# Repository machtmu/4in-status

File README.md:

# Status Module Repository

---

<div align="center">
  <div>

    <p><em>3D Render</em></p>
  </div>
  <br>

  <div>
    <br>
    <p><em>Schematic</em></p>
  </div>
  <br>
  
  <div>
    
    <br>
    <em>Footprint</em>
  </div>
</div>

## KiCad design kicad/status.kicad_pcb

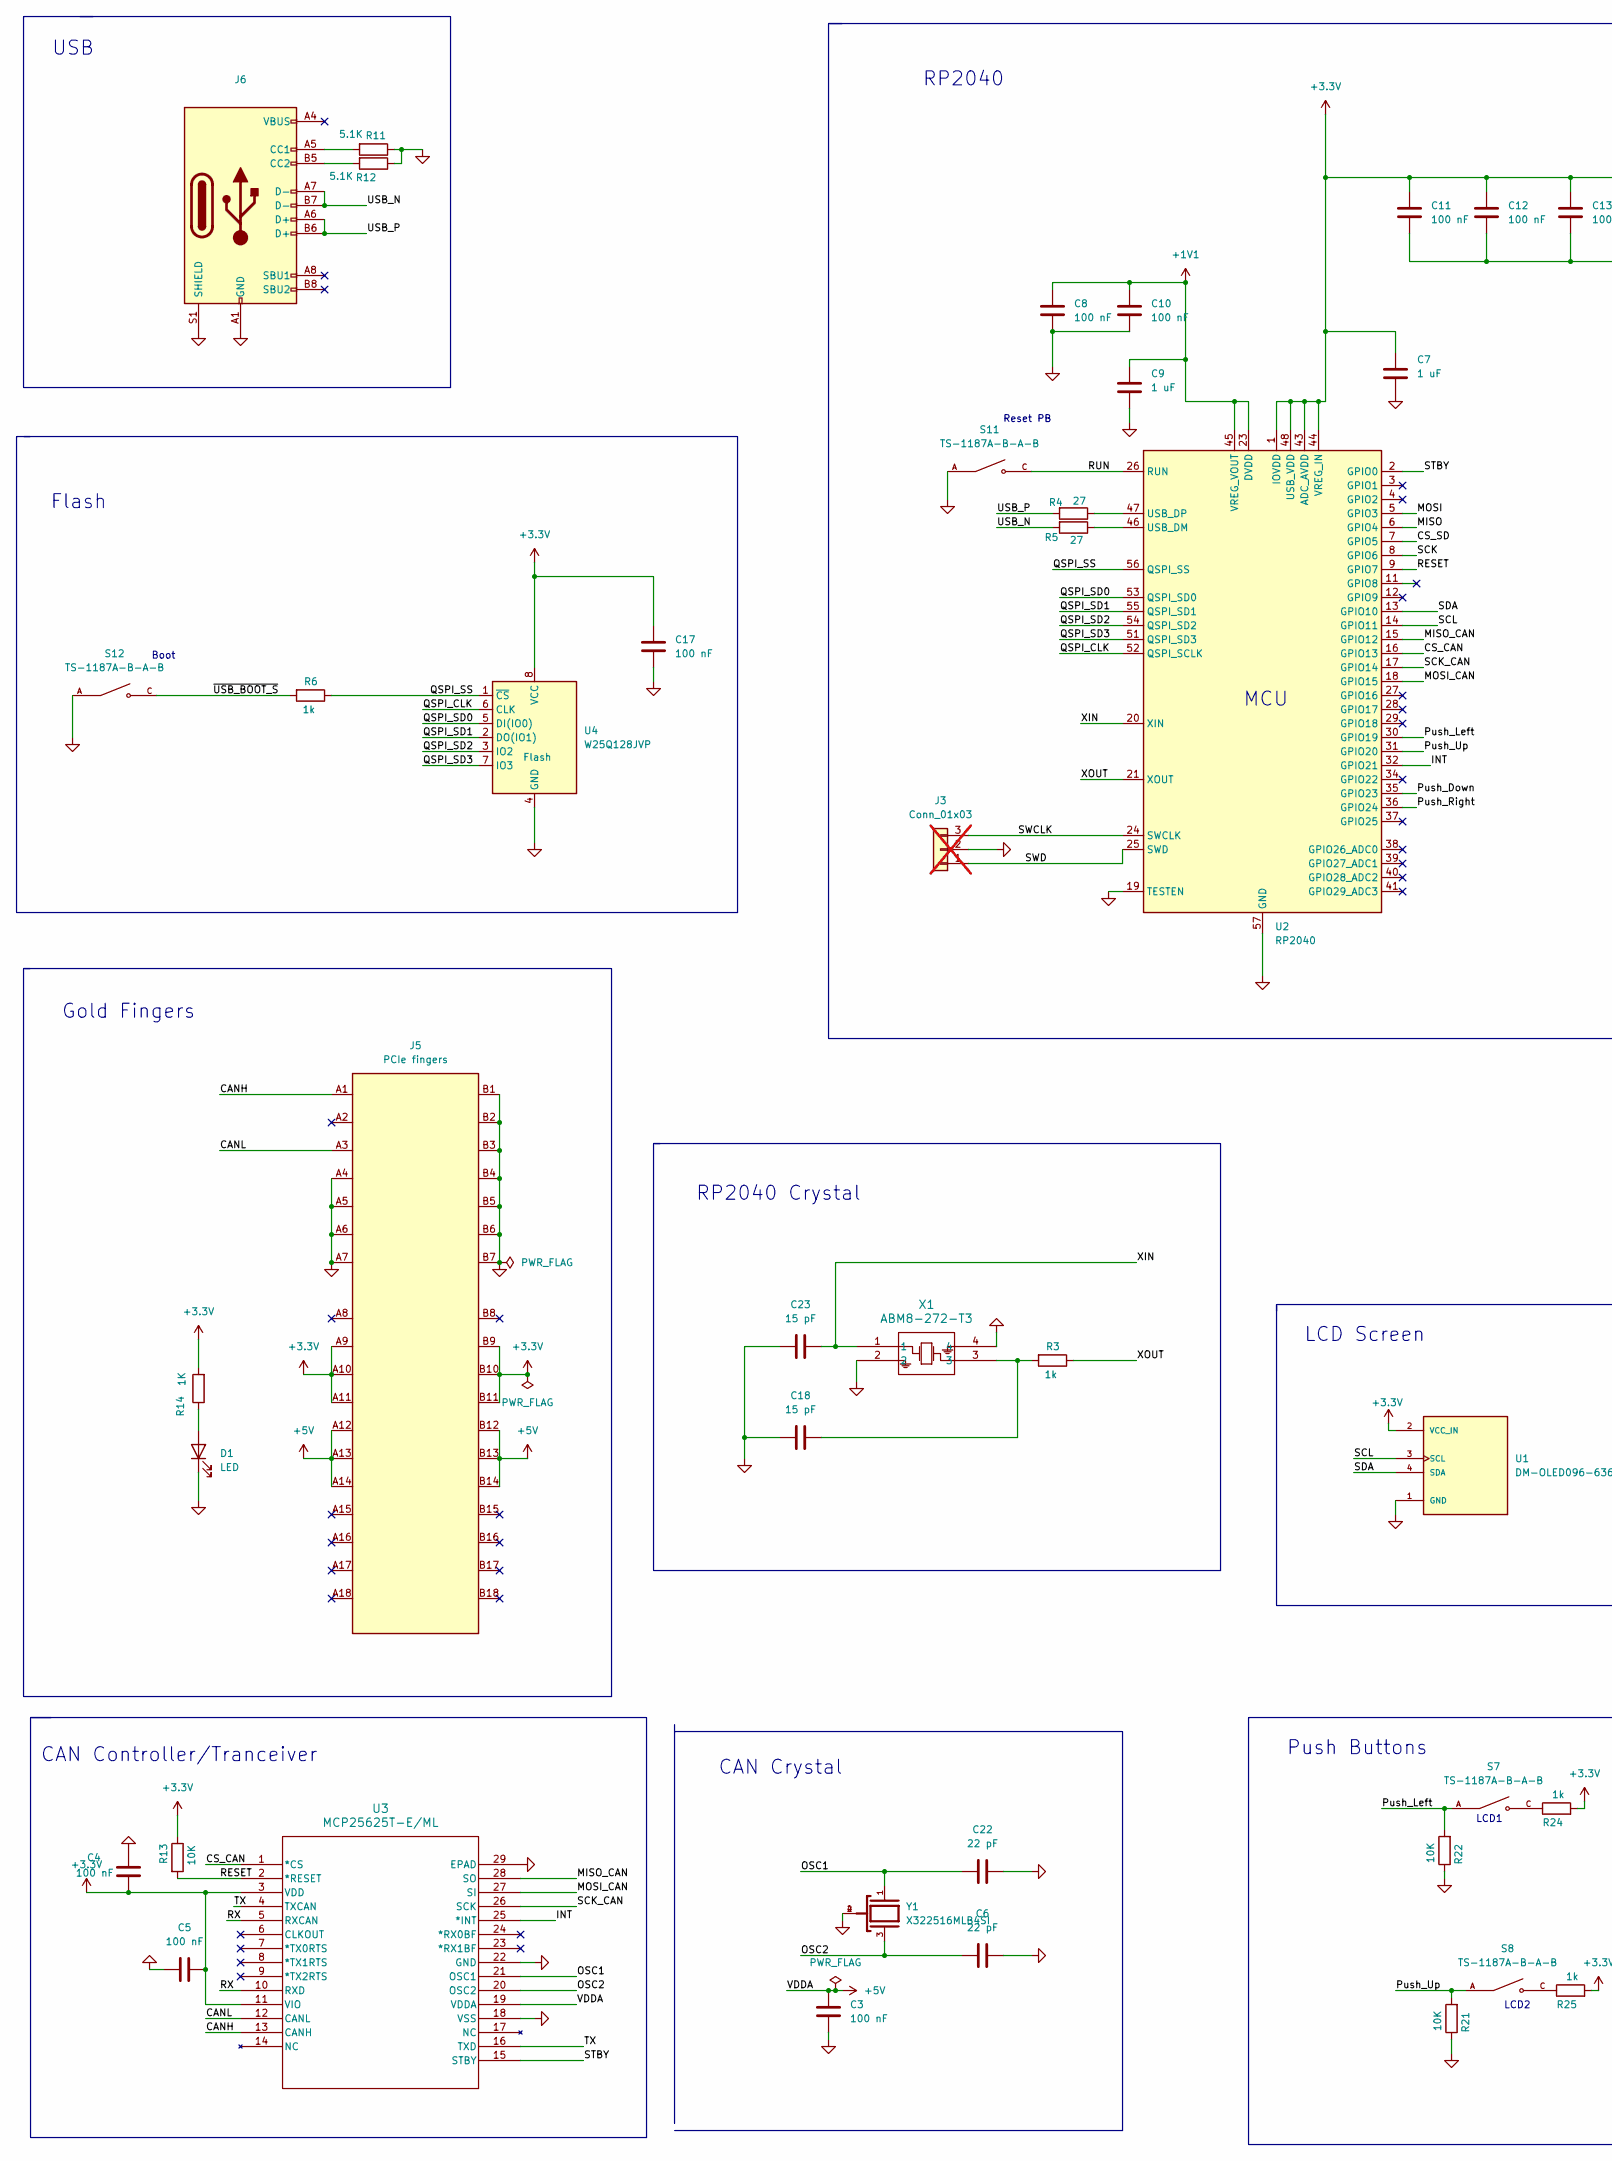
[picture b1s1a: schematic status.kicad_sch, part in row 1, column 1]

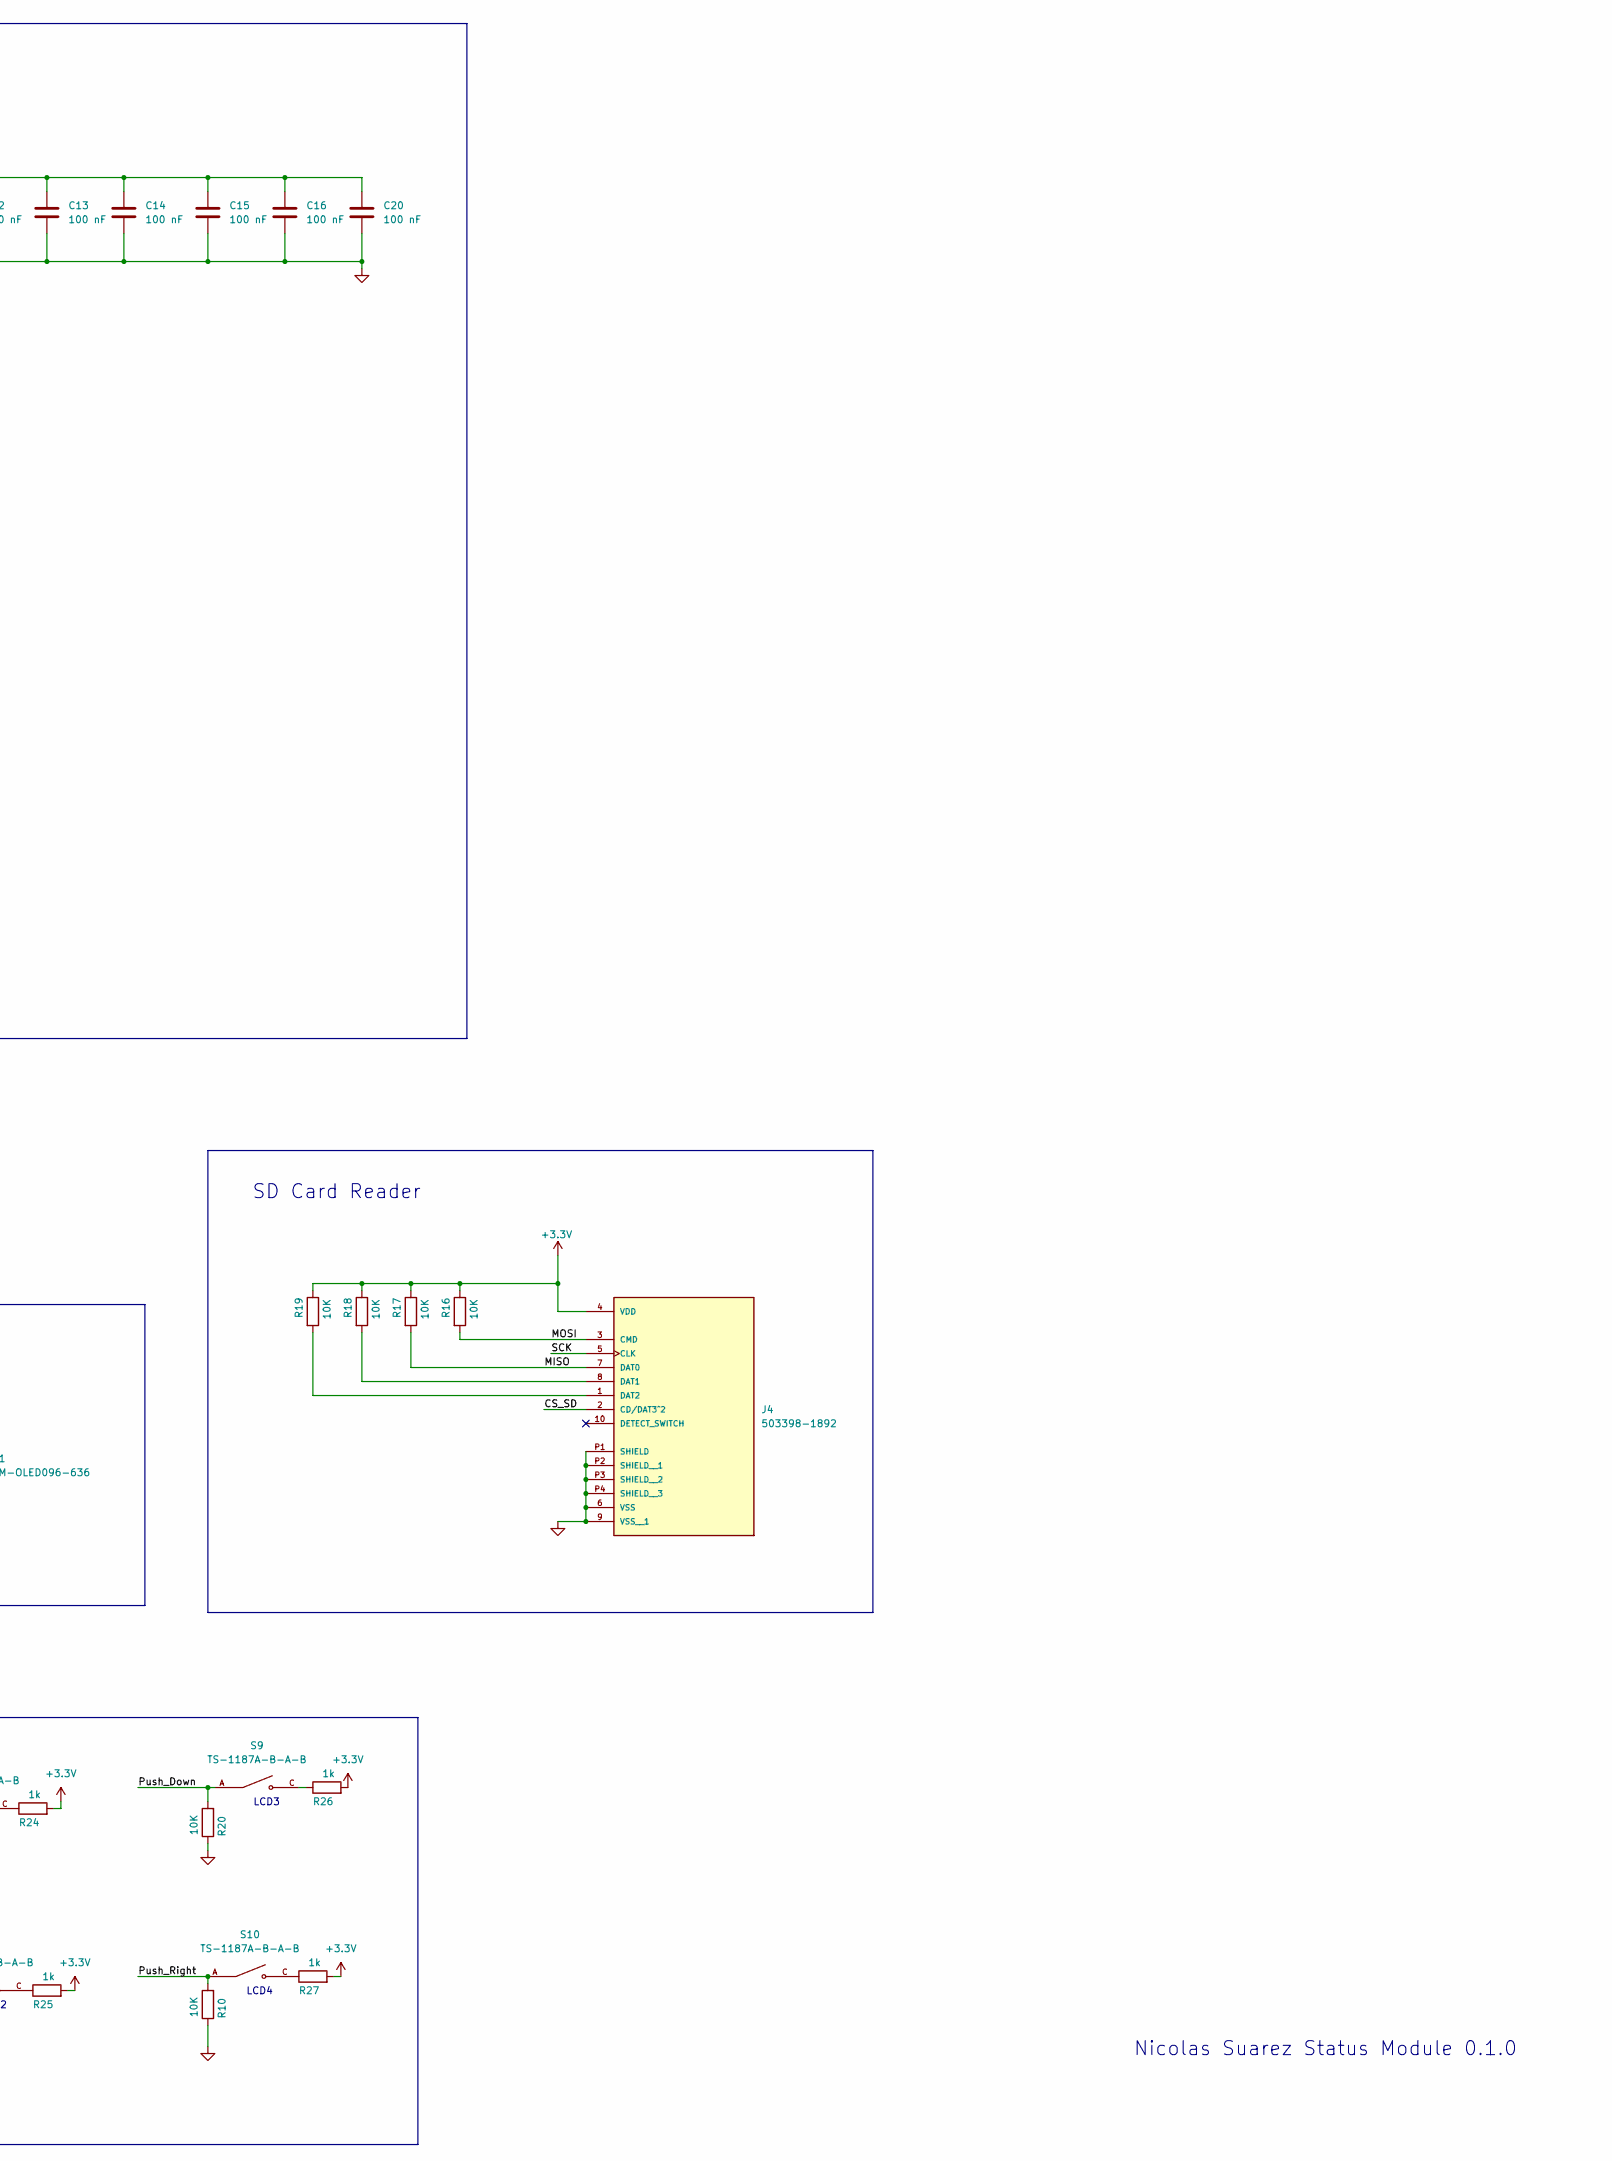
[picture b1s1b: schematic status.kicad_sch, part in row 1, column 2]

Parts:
C3, C4, C5, C8, C10, C11, C12, C13, C14, C15, C16, C17, C20: 100 nF; C_0402_1005Metric; LCSC Part # C307331
C6, C22: 22 pF; C_0402_1005Metric; LCSC Part # C70464
C7, C9: 1 uF; C_0402_1005Metric; LCSC Part # C52923
C18, C23: 15 pF; C_0402_1005Metric; LCSC Part # C1548
D1: LED; LED_0402_1005Metric; LCSC Part # C74340
J3: Conn_01x03; PinHeader_1x03_P2.54mm_Vertical; not fitted
J4: 503398-1892; MOLEX_503398-1892; PARTREV 0; JLCPCB Part # C428492
J5: Bus_PCI_Express_x1; BUS_PCIexpress_x1; LCSC Part # n/a
J6: USB_C_Receptacle_USB2.0_16P; USB_C_Receptacle_Palconn_UTC16-G; LCSC Part # C2765186
R3, R6, R24, R25, R26, R27: 1k; R_0402_1005Metric; LCSC Part # C11702
R4, R5: 27; R_0402_1005Metric; LCSC Part # C25100
R10, R13, R16, R17, R18, R19, R20, R21, R22: 10K; R_0402_1005Metric; LCSC Part # C60490
R11, R12: 5.1K; R_0402_1005Metric; LCSC Part # C25905
R14: 1K; R_0402_1005Metric; LCSC Part # C71623
S7, S8, S9, S10, S11, S12: TS-1187A-B-A-B; SW_TS-1187A-B-A-B; PARTREV A0; LCSC Part # C318884
U1: DM-OLED096-636; MODULE_DM-OLED096-636; PARTREV 2018-09-10
U2: RP2040; QFN-56-1EP_7x7mm_P0.4mm_EP3.2x3.2mm; LCSC C2040
U3: MCP25625T-E/ML; QFN28_6X6MC_MCH; LCSC Part # C191253
U4: W25Q128JVP; WSON-8-1EP_6x5mm_P1.27mm_EP3.4x4.3mm; LCSC C190862
X1: ABM8-272-T3; ABM8-272-T3_ABR; LCSC Part # C20625731
Y1: X322516MLB4SI; OSC_X322516MLB4SI; PARTREV N/A; LCSC Part # C13738

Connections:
+1V1: C8.2, C9.2, C10.2, U2.23 (DVDD), U2.45 (VREG_VOUT), U2.50 (DVDD)
+3.3V: C4.1, C5.1, C7.2, C11.2, C12.2, C13.2, C14.2, C15.2, C16.2, C17.2, C20.2, J4.4 (VDD), J5.A9 (+3.3V), J5.A10 (+3.3V), J5.A11 (~PERST), J5.B9 (JTAG1), J5.B10 (3.3Vaux), J5.B11 (~WAKE), R13.1, R14.2, R16.1, R17.1, R18.1, R19.1, R24.2, R25.2, R26.2, R27.2, U1.2 (VCC_IN), U2.1 (IOVDD), U2.10 (IOVDD), U2.22 (IOVDD), U2.33 (IOVDD), U2.42 (IOVDD), U2.43 (ADC_AVDD), U2.44 (VREG_IN), U2.48 (USB_VDD), U2.49 (IOVDD), U3.3 (VDD), U3.11 (VIO), U4.8 (VCC)
+5V: C3.2, J5.A12 (GND), J5.A13 (REFCLK+), J5.A14 (REFCLK-), J5.B12 (RSVD), J5.B13 (GND), J5.B14 (PETp0), U3.19 (VDDA)
/CANH: J5.A1 (~PRSNT1), U3.13 (CANH)
/CANL: J5.A3 (+12V), U3.12 (CANL)
/CS_CAN: U2.16 (GPIO13), U3.1 (*CS)
/CS_SD: J4.2 (CD/DAT3^2), U2.7 (GPIO5)
/INT: U2.32 (GPIO21), U3.25 (*INT)
/MISO: J4.7 (DAT0), R17.2, U2.6 (GPIO4)
/MISO_CAN: U2.15 (GPIO12), U3.28 (SO)
/MOSI: J4.3 (CMD), R16.2, U2.5 (GPIO3)
/MOSI_CAN: U2.18 (GPIO15), U3.27 (SI)
/OSC1: C22.2, U3.21 (OSC1), Y1.1
/OSC2: C6.2, U3.20 (OSC2), Y1.3
/Push_Down: R20.2, S9.A, U2.35 (GPIO23)
/Push_Left: R22.2, S7.A, U2.30 (GPIO19)
/Push_Right: R10.2, S10.A, U2.36 (GPIO24)
/Push_Up: R21.2, S8.A, U2.31 (GPIO20)
/QSPI_CLK: U2.52 (QSPI_SCLK), U4.6 (CLK)
/QSPI_SD0: U2.53 (QSPI_SD0), U4.5 (DI(IO0))
/QSPI_SD1: U2.55 (QSPI_SD1), U4.2 (DO(IO1))
/QSPI_SD2: U2.54 (QSPI_SD2), U4.3 (IO2)
/QSPI_SD3: U2.51 (QSPI_SD3), U4.7 (IO3)
/QSPI_SS: R6.1, U2.56 (QSPI_SS), U4.1 (~CS)
/RESET: R13.2, U2.9 (GPIO7), U3.2 (*RESET)
/RUN: S11.C, U2.26 (RUN)
/RX: U3.5 (RXCAN), U3.10 (RXD)
/SCK: J4.5 (CLK), U2.8 (GPIO6)
/SCK_CAN: U2.17 (GPIO14), U3.26 (SCK)
/SCL: U1.3 (SCL), U2.14 (GPIO11)
/SDA: U1.4 (SDA), U2.13 (GPIO10)
/STBY: U2.2 (GPIO0), U3.15 (STBY)
/SWCLK: J3.3, U2.24 (SWCLK)
/SWD: J3.1, U2.25 (SWD)
/TX: U3.4 (TXCAN), U3.16 (TXD)
/USB_N: J6.A7 (D-), J6.B7 (D-), R5.2
/USB_P: J6.A6 (D+), J6.B6 (D+), R4.2
/XIN: C23.1, U2.20 (XIN), X1.1
/XOUT: R3.1, U2.21 (XOUT)
/~USB_BOOT_S: R6.2, S12.C
GND: C3.1, C4.2, C5.2, C6.1, C7.1, C8.1, C9.1, C10.1, C11.1, C12.1, C13.1, C14.1, C15.1, C16.1, C17.1, C18.2, C20.1, C22.1, C23.2, D1.1 (K), J3.2, J4.6 (VSS), J4.9 (VSS__1), J4.P1 (SHIELD), J4.P2 (SHIELD__1), J4.P3 (SHIELD__2), J4.P4 (SHIELD__3), J5.A4 (GND), J5.A5 (JTAG2), J5.A6 (JTAG3), J5.A7 (JTAG4), J5.B1 (+12V), J5.B2 (+12V), J5.B3 (+12V), J5.B4 (GND), J5.B5 (SMCLK), J5.B6 (SMDAT), J5.B7 (GND), J6.A1 (GND), J6.A12 (GND), J6.B1 (GND), J6.B12 (GND), J6.S1 (SHIELD), R10.1, R11.1, R12.1, R20.1, R21.1, R22.1, S11.A, S12.A, U1.1 (GND), U2.19 (TESTEN), U2.57 (GND), U3.18 (VSS), U3.22 (GND), U3.29 (EPAD), U4.4 (GND), X1.2, X1.4, Y1.2, Y1.4
unnamed: C18.1, R3.2, X1.3
unnamed: D1.2 (A), R14.1
unnamed: J4.8 (DAT1), R18.2
unnamed: J4.1 (DAT2), R19.2
unnamed: J6.A5 (CC1), R11.2
unnamed: J6.B5 (CC2), R12.2
unnamed: R24.1, S7.C
unnamed: R25.1, S8.C
unnamed: R26.1, S9.C
unnamed: R27.1, S10.C
unnamed: R5.1, U2.46 (USB_DM)
unnamed: R4.1, U2.47 (USB_DP)

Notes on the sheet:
LCD2
SD Card Reader
LCD1
RP2040 Crystal
USB
CAN Crystal
MCU
Boot
Nicolas Suarez Status Module 0.1.0
RP2040
LCD Screen
Gold Fingers
LCD4
Push Buttons
LCD3
Reset PB
CAN Controller/Tranceiver
Flash

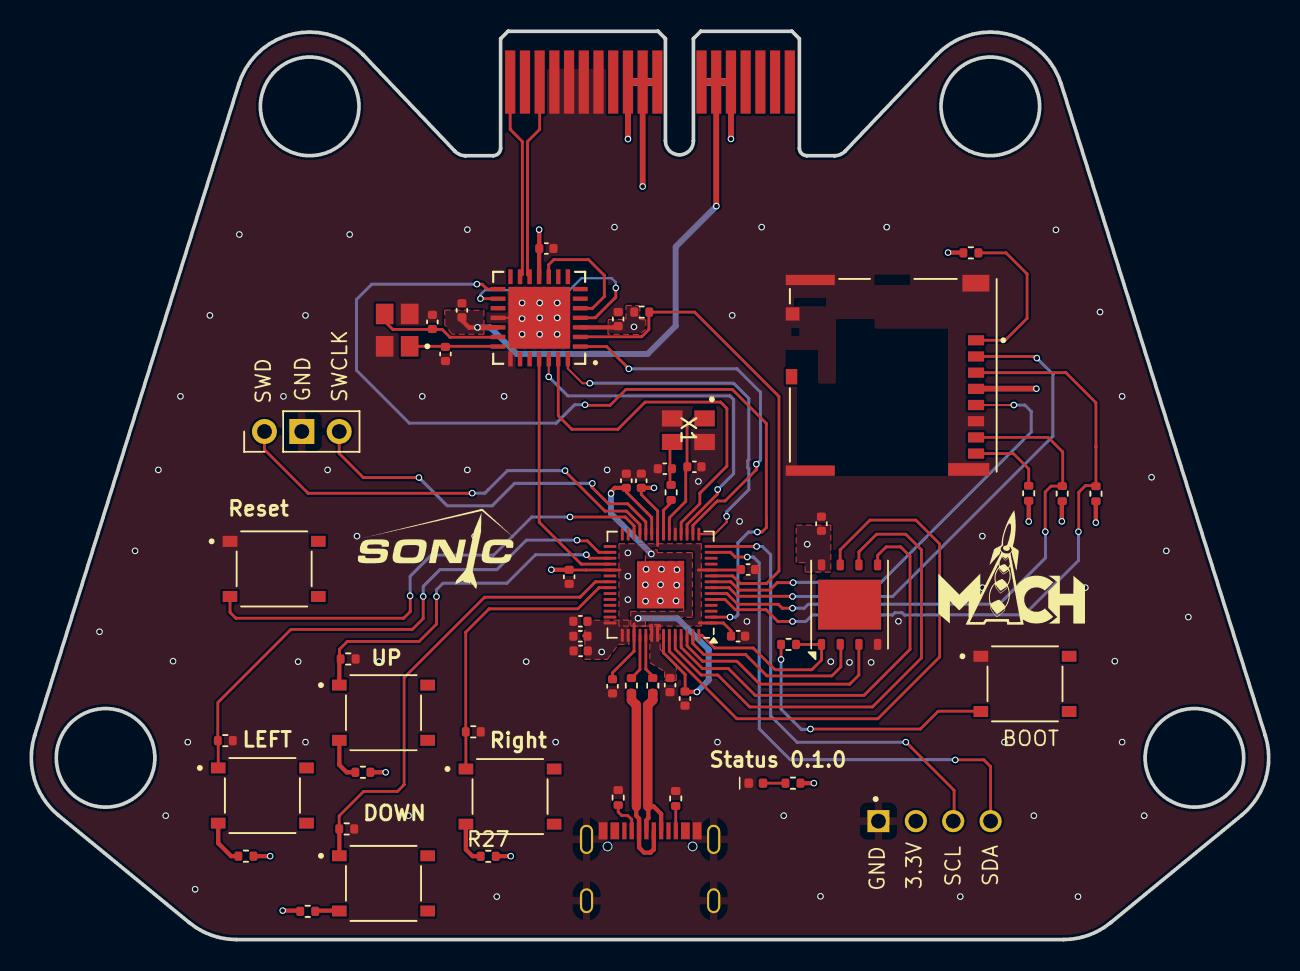
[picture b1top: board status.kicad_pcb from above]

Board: 4 copper layers, 84.1 x 61.7 mm, 56 parts (1 on the bottom side), 53 nets.

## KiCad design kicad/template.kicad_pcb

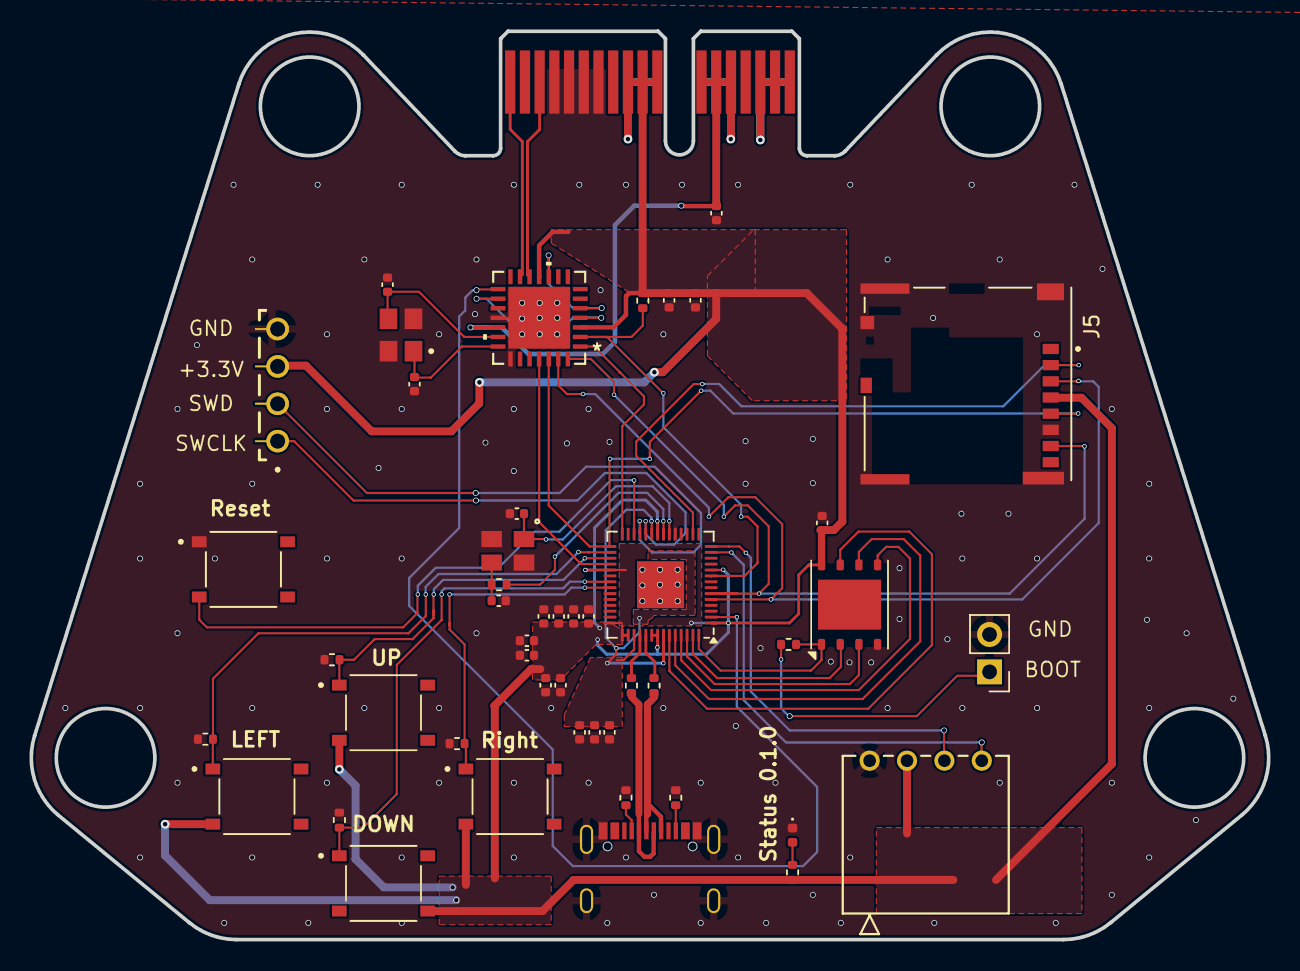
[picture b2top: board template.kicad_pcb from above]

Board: 2 copper layers, 84.1 x 61.7 mm, 48 parts (1 on the bottom side), 45 nets.

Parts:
C3, C4, C5, C8, C10, C11, C12, C13, C14, C15, C16, C17, C20: 100 nF; C_0402_1005Metric
C6, C22: 22 pF; C_0402_1005Metric
C7, C9: 1 uF; C_0402_1005Metric
C18, C23: 15 pF; C_0402_1005Metric
D1: LED; LED_0402_1005Metric
J1: Bus_PCI_Express_x1; BUS_PCIexpress_x1
J2: PPTC041LGBN-RC; CONN_PPTC041LGBN-RC_SUL
J3: Conn_01x04; SAMTEC_MTLW-104-X-X-S-X
J5: 503398-1892; MOLEX_503398-1892
J6: USB_C_Receptacle_USB2.0_16P; USB_C_Receptacle_Palconn_UTC16-G
J7: Conn_01x02; PinHeader_1x02_P2.54mm_Vertical
R3, R6: 1k; R_0402_1005Metric
R4, R5: 27; R_0402_1005Metric
R7, R8, R9, R10, R13: 10K; R_0402_1005Metric
R11, R12: 5.1K; R_0402_1005Metric
R14: 1K; R_0402_1005Metric
S7, S8, S9, S10, S11: TS-1187A-B-A-B; SW_TS-1187A-B-A-B
U1: MCP25625T-E/ML; QFN28_6X6MC_MCH
U2: RP2040; QFN-56-1EP_7x7mm_P0.4mm_EP3.2x3.2mm
U4: W25Q128JVP; WSON-8-1EP_6x5mm_P1.27mm_EP3.4x4.3mm
X1: ABM8-272-T3; ABM8-272-T3_ABR
Y1: X322516MLB4SI; OSC_X322516MLB4SI

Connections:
+1V1: C8.2, C9.2, C10.2, U2.23 (DVDD), U2.45 (VREG_VOUT), U2.50 (DVDD)
+3.3V: C4.1, C5.1, C7.2, C11.2, C12.2, C13.2, C14.2, C15.2, C16.2, C17.2, C20.2, J1.A9 (+3.3V), J1.A10 (+3.3V), J1.A11 (~PERST), J1.B9 (JTAG1), J1.B10 (3.3Vaux), J1.B11 (~WAKE), J2.2, J3.3, J5.4 (VDD), R13.1, R14.2, S7.C, S8.C, S9.D, S10.C, U1.3 (VDD), U1.11 (VIO), U2.1 (IOVDD), U2.10 (IOVDD), U2.22 (IOVDD), U2.33 (IOVDD), U2.42 (IOVDD), U2.43 (ADC_AVDD), U2.44 (VREG_IN), U2.48 (USB_VDD), U2.49 (IOVDD), U4.8 (VCC)
+5V: C3.2, J1.A12 (GND), J1.A13 (REFCLK+), J1.A14 (REFCLK-), J1.B12 (RSVD), J1.B13 (GND), J1.B14 (PETp0), U1.19 (VDDA)
+BAT: J1.A16 (PERp0), J1.A17 (PERn0), J1.A18 (GND), J1.B16 (GND), J1.B17 (~PRSNT2), J1.B18 (GND)
/CANH: J1.A1 (~PRSNT1), U1.13 (CANH)
/CANL: J1.A3 (+12V), U1.12 (CANL)
/CS: U1.1 (*CS), U2.28 (GPIO17)
/CS_SD: J5.2 (CD/DAT3^2), U2.16 (GPIO13)
/INT: U1.25 (*INT), U2.32 (GPIO21)
/MISO: J5.7 (DAT0), U1.28 (SO), U2.6 (GPIO4)
/MOSI: J5.3 (CMD), U1.27 (SI), U2.5 (GPIO3)
/OSC1: C22.2, U1.21 (OSC1), Y1.1
/OSC2: C6.2, U1.20 (OSC2), Y1.3
/Push_Down: R8.1, S9.A, U2.35 (GPIO23)
/Push_Left: R7.1, S7.A, U2.30 (GPIO19)
/Push_Right: R9.1, S10.A, U2.36 (GPIO24)
/Push_Up: R10.1, S8.A, U2.31 (GPIO20)
/QSPI_CLK: U2.52 (QSPI_SCLK), U4.6 (CLK)
/QSPI_SD0: U2.53 (QSPI_SD0), U4.5 (DI(IO0))
/QSPI_SD1: U2.55 (QSPI_SD1), U4.2 (DO(IO1))
/QSPI_SD2: U2.54 (QSPI_SD2), U4.3 (IO2)
/QSPI_SD3: U2.51 (QSPI_SD3), U4.7 (IO3)
/QSPI_SS: R6.1, U2.56 (QSPI_SS), U4.1 (~CS)
/RESET: R13.2, U1.2 (*RESET), U2.9 (GPIO7)
/RX: U1.5 (RXCAN), U1.10 (RXD)
/SCK: J5.5 (CLK), U1.26 (SCK), U2.29 (GPIO18)
/SCL: J2.3, U2.14 (GPIO11)
/SDA: J2.4, U2.13 (GPIO10)
/STBY: U1.15 (STBY), U2.2 (GPIO0)
/SWCLK: J3.1, U2.24 (SWCLK)
/SWD: J3.2, U2.25 (SWD)
/TX: U1.4 (TXCAN), U1.16 (TXD)
/USB_N: J6.A7 (D-), J6.B7 (D-), R5.2
/USB_P: J6.A6 (D+), J6.B6 (D+), R4.2
/X_IN: C23.1, U2.20 (XIN), X1.1
/X_OUT: R3.1, U2.21 (XOUT)
/~USB_BOOT_S: J7.1, R6.2
GND: C3.1, C4.2, C5.2, C6.1, C7.1, C8.1, C9.1, C10.1, C11.1, C12.1, C13.1, C14.1, C15.1, C16.1, C17.1, C18.2, C20.1, C22.1, C23.2, D1.1 (K), J1.A4 (GND), J1.A5 (JTAG2), J1.A6 (JTAG3), J1.A7 (JTAG4), J1.B1 (+12V), J1.B2 (+12V), J1.B3 (+12V), J1.B4 (GND), J1.B5 (SMCLK), J1.B6 (SMDAT), J1.B7 (GND), J2.1, J3.4, J5.6 (VSS), J5.9 (VSS__1), J5.P1 (SHIELD), J5.P2 (SHIELD__1), J5.P3 (SHIELD__2), J5.P4 (SHIELD__3), J6.A1 (GND), J6.A12 (GND), J6.B1 (GND), J6.B12 (GND), J6.S1 (SHIELD), J7.2, R7.2, R8.2, R9.2, R10.2, R11.1, R12.1, S11.A, U1.18 (VSS), U1.22 (GND), U1.29 (EPAD), U2.19 (TESTEN), U2.57 (GND), U4.4 (GND), X1.2, X1.4, Y1.2, Y1.4
unnamed: C18.1, R3.2, X1.3
unnamed: D1.2 (A), R14.1
unnamed: J6.A5 (CC1), R11.2
unnamed: J6.B5 (CC2), R12.2
unnamed: S11.C, U2.26 (RUN)
unnamed: R5.1, U2.46 (USB_DM)
unnamed: R4.1, U2.47 (USB_DP)

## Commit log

2025-03-03 Update images
2025-03-03 init status module
2025-03-14 Update schematic
2025-03-20 update schematic and pcb layout
2025-03-24 update BOM
2025-05-16 Changed Schematic
2025-05-22 Update PCB Layout
2025-05-23 PCB Layout update
2025-05-31 Update PCB Layout and Change file Names to Status
2025-06-07 Updated PCB Layout
2025-06-07 update rack dxf outline
2025-06-14 PCB Update
2025-07-22 Pcb layout updated
2025-08-04 SD Card Update
2025-08-05 General Updates
    Moved CAN transmitter to separate SPI line.
    Updated rp2040 clock.
    Fixed debug pins.
    Updated nets.
2025-08-05 General update schematic and PCB
2025-08-27 Fxed 3d Body PB
2025-08-27 updated schematic
2025-08-27 added silkscreen to LCD screen pins
2025-08-27 Updated silkscreen
2025-08-28 Rename repository from Template to Status Module
2025-09-06 Changes on the PCB layout
2025-09-09 Organized schematic into functional blocks
2025-09-14 PCB layout changes
2025-10-05 Added JLCPCB Design Rules and Fixed DRCs
2025-10-05 Fixed DRCs
2025-11-21 Change workflow reference from sonicavionics to machtmu
